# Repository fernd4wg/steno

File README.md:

# CUSTOM RP20240 STENOGRAPHY KEYBOARD

More keyboard schtuff.
Better PCB design.
Using RP2040 chip rather than the microcontroller.
Cool.

AWESOME!

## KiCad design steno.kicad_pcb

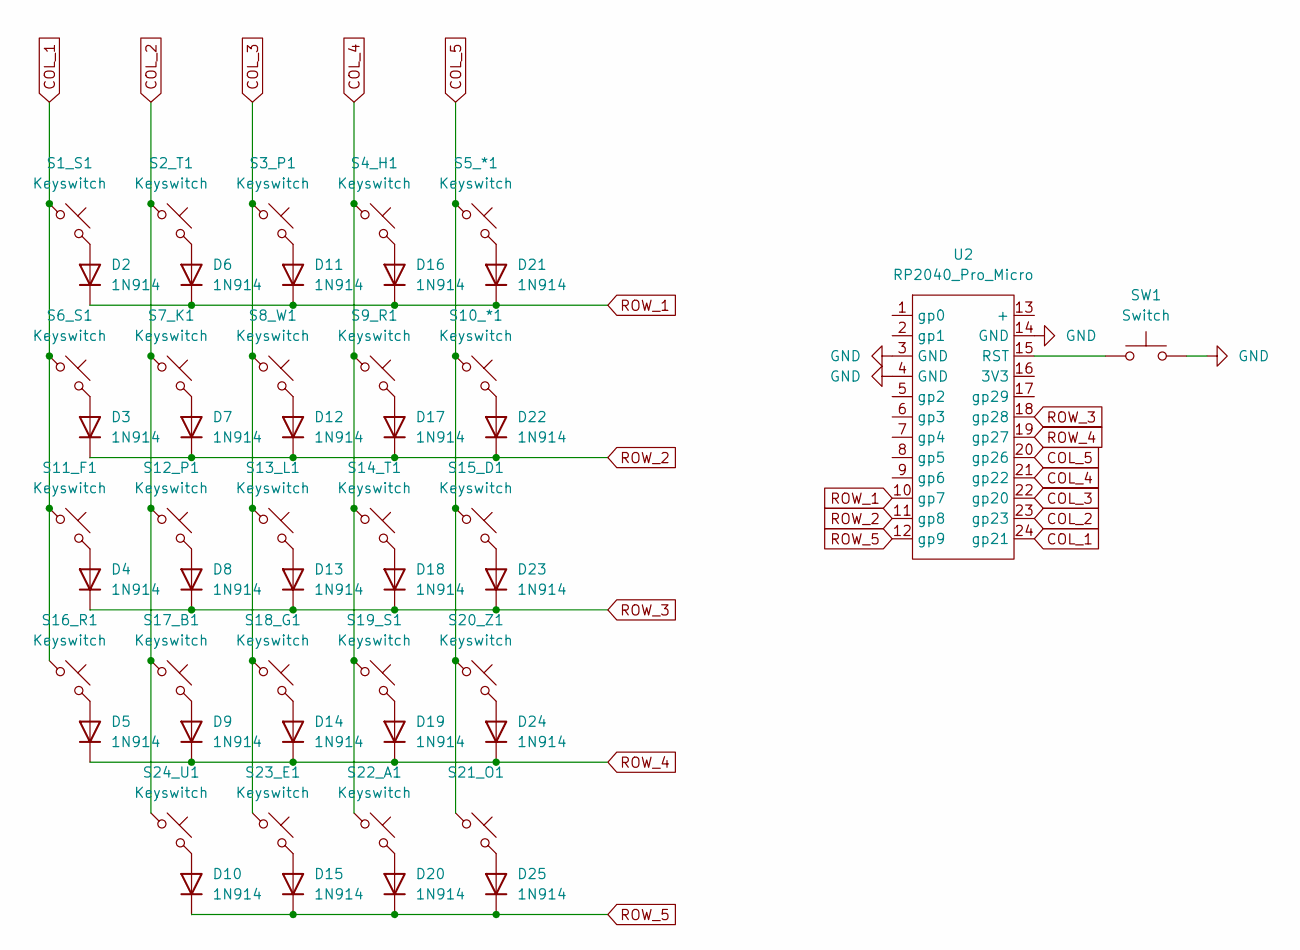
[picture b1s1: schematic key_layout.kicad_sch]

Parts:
D2, D3, D4, D5, D6, D7, D8, D9, D10, D11, D12, D13, D14, D15, D16, D17, D18, D19, D20, D21, D22, D23, D24, D25: 1N914; D_SOD-123
S1_S1, S2_T1, S3_P1, S4_H1, S5_*1, S6_S1, S7_K1, S8_W1, S9_R1, S10_*1, S11_F1, S12_P1, S13_L1, S14_T1, S15_D1, S16_R1, S17_B1, S18_G1, S19_S1, S20_Z1, S21_O1, S22_A1, S23_E1, S24_U1: Keyswitch; Hotswap_Choc_V1V2_1.00u
SW1: Switch; SW_SPST_PTS810
U2: RP2040_Pro_Micro

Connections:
COL_1: S1_S1.1, S6_S1.1, S11_F1.1, S16_R1.1, U2.24 (gp21)
COL_2: S2_T1.1, S7_K1.1, S12_P1.1, S17_B1.1, S24_U1.1, U2.23 (gp23)
COL_3: S3_P1.1, S8_W1.1, S13_L1.1, S18_G1.1, S23_E1.1, U2.22 (gp20)
COL_4: S4_H1.1, S9_R1.1, S14_T1.1, S19_S1.1, S22_A1.1, U2.21 (gp22)
COL_5: S5_*1.1, S10_*1.1, S15_D1.1, S20_Z1.1, S21_O1.1, U2.20 (gp26)
GND: SW1.2, U2.3 (GND), U2.4 (GND), U2.14 (GND)
unnamed: D2.2 (A), S1_S1.2
unnamed: D3.2 (A), S6_S1.2
unnamed: D4.2 (A), S11_F1.2
unnamed: D5.2 (A), S16_R1.2
unnamed: D6.2 (A), S2_T1.2
unnamed: D7.2 (A), S7_K1.2
unnamed: D8.2 (A), S12_P1.2
unnamed: D9.2 (A), S17_B1.2
unnamed: D10.2 (A), S24_U1.2
unnamed: D11.2 (A), S3_P1.2
unnamed: D12.2 (A), S8_W1.2
unnamed: D13.2 (A), S13_L1.2
unnamed: D14.2 (A), S18_G1.2
unnamed: D15.2 (A), S23_E1.2
unnamed: D16.2 (A), S4_H1.2
unnamed: D17.2 (A), S9_R1.2
unnamed: D18.2 (A), S14_T1.2
unnamed: D19.2 (A), S19_S1.2
unnamed: D20.2 (A), S22_A1.2
unnamed: D21.2 (A), S5_*1.2
unnamed: D22.2 (A), S10_*1.2
unnamed: D23.2 (A), S15_D1.2
unnamed: D24.2 (A), S20_Z1.2
unnamed: D25.2 (A), S21_O1.2
unnamed: SW1.1, U2.15 (RST)
ROW_1: D2.1 (K), D6.1 (K), D11.1 (K), D16.1 (K), D21.1 (K), U2.10 (gp7)
ROW_2: D3.1 (K), D7.1 (K), D12.1 (K), D17.1 (K), D22.1 (K), U2.11 (gp8)
ROW_3: D4.1 (K), D8.1 (K), D13.1 (K), D18.1 (K), D23.1 (K), U2.18 (gp28)
ROW_4: D5.1 (K), D9.1 (K), D14.1 (K), D19.1 (K), D24.1 (K), U2.19 (gp27)
ROW_5: D10.1 (K), D15.1 (K), D20.1 (K), D25.1 (K), U2.12 (gp9)

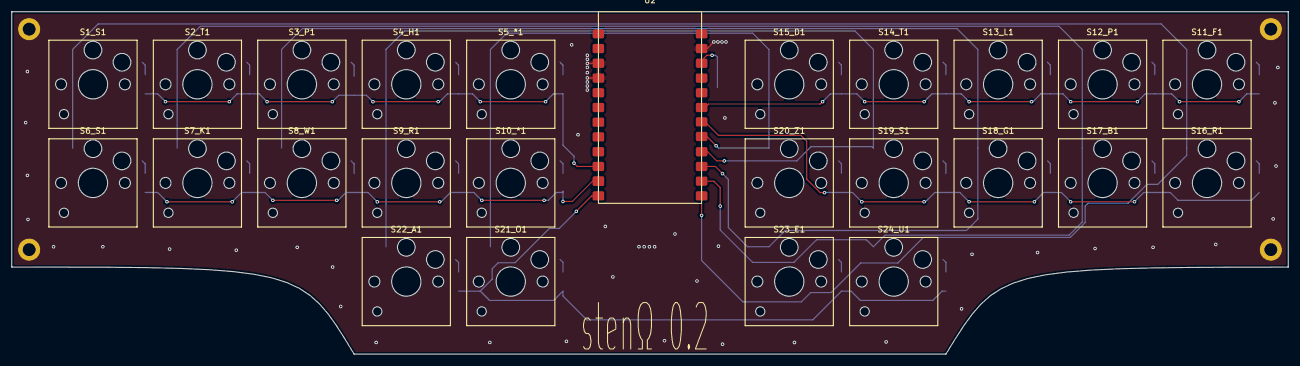
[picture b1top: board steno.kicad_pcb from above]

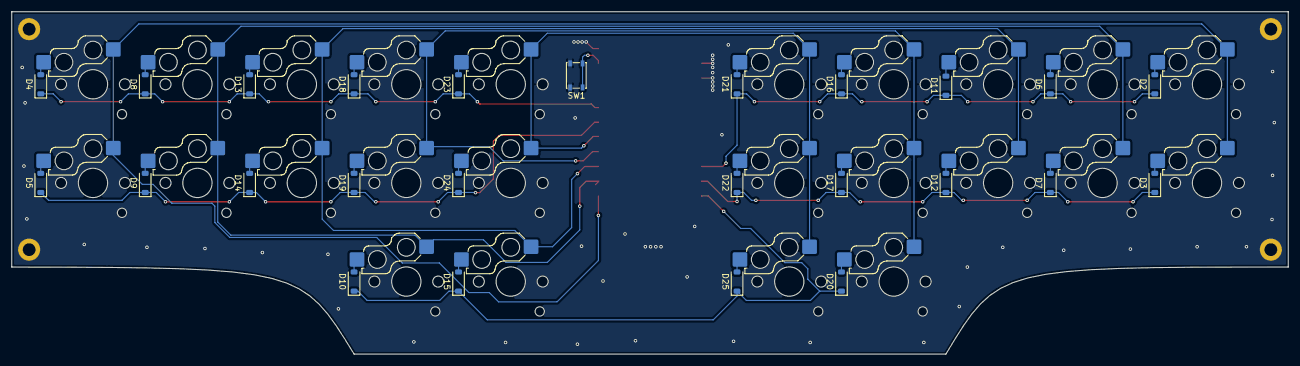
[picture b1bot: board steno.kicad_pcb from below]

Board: 2 copper layers, 220.0 x 59.0 mm, 50 parts (25 on the bottom side), 36 nets.

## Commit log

2026-05-02 Savepoint!
2026-05-15 Smalled Caps and Restarting Layout.
2026-05-16 Layout changes & wiring testing
2026-05-16 Updated images!
2026-05-16 More images & orginization
2026-05-16 Organizing documentation
2026-05-19 Organizing docs
2026-05-21 Test
2026-05-22 Fixing buttons / Transitioning to new computer.
2026-05-23 added status LED / Potential final changes
2026-05-31 Made changes based on feedback and RP2040 doc.
2026-05-31 Updating images.
2026-05-31 Gerber plot(s) and drill files.
2026-06-14 Init Commit!
